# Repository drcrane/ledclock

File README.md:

LEDCLOCK
========

This repository contains the source files for my seven segment LED
Clock which I made in 2017 for my nephew.

The Clock is powered by an MSP430G2553 and a 32.768 kHz watch
crystal. The clock queried time over the serial port which should
be connected to an ESP8266 (ESP-01) running a modified terminal
programme that supports querying internet time servers.

Running ntpd on Alpine Linux
----------------------------

Turn on a time server in Alpine Linux / busybox (if compiled in)

    busybox ntpd -l -d -d -d -n

This is good for testing as you can see each request for the time.

ESP8266\_RTOS\_SDK
------------------

`esp8266terminal2` uses the espressif SDK, please see readme file
in `esp8266terminal2`.

 - Benjamin Green 2021-12-31

Open-RTOS-SDK
-------------

`esp8266terminal` is no longer used for this project and will be
removed soon. Please use `esp8266terminal2`.

The terminal application was modified (not very well) to support
this application. The REPOs:

repo:   https://github.com/SuperHouse/esp-open-rtos
commit: 46499c0f26c490f5a539f82eb950fa7879f65dc7

repo:   https://github.com/pfalcon/esp-open-sdk
commit: 5518fb6116c35a02ccb9a87260bb194a57cb429e

The build scripts and programmer are required from the above
repos.

The modified terminal application is available in:
`esp8266terminal` I recommend that you copy this into the
`esp-open-rtos/examples` directory to compile and deploy to
an ESP8266.

 - Benjamin Green 2018-02-03

Web Interface Time Setting
--------------------------

To set the time for a clock that currently has an IP address of `192.168.0.128`

    curl -v -d time_to_set=23:50:00 http://192.168.0.128/wifi

A browser may also be used by accessing the page at: `http://192.168.0.128/wifi`.

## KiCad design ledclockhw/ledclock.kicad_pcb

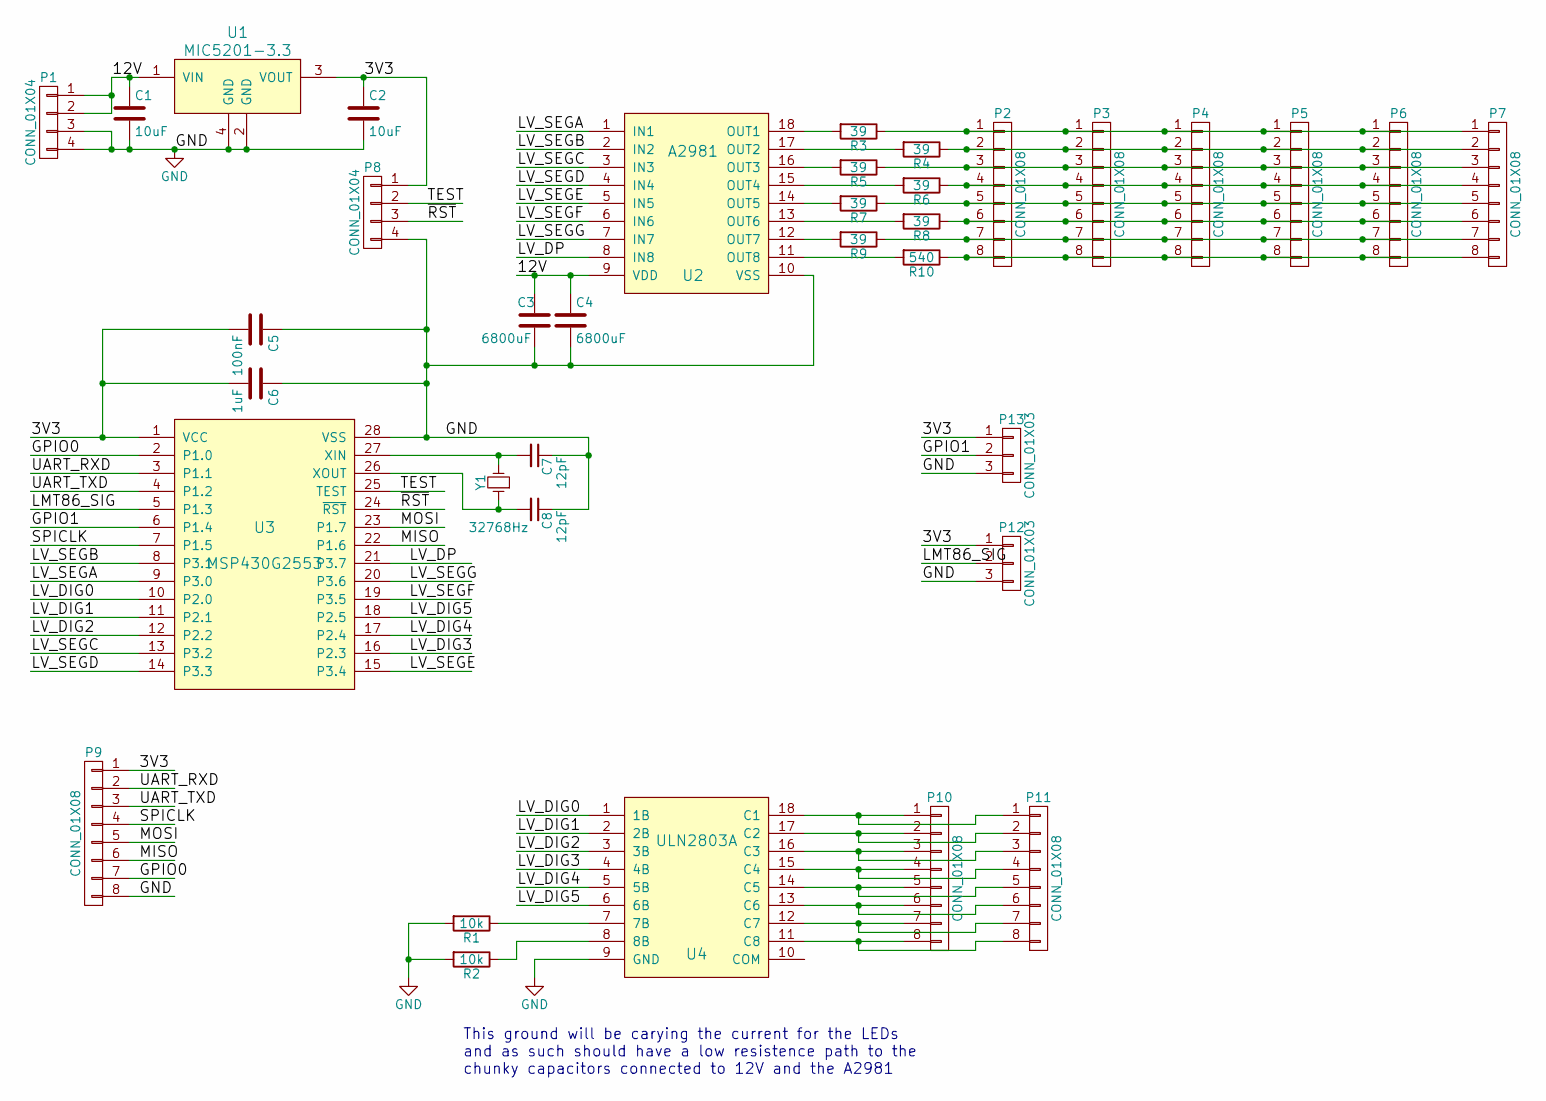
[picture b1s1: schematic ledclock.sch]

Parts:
C1, C2: 10uF; C_1210
C3, C4: 6800uF; CP_Radial_D18.0mm_P7.50mm
C5: 100nF; C_0603
C6: 1uF; C_0805
C7, C8: 12pF; C_0603
P1, P8: CONN_01X04; Molex_KK-6410-04_04x2.54mm_Straight
P2, P3, P4, P5, P6, P7, P9, P10, P11: CONN_01X08; Molex_KK-6410-08_08x2.54mm_Straight
P12, P13: CONN_01X03; Molex_KK-6410-03_03x2.54mm_Straight
R1, R2: 10k; R_0603
R3, R4, R5, R6, R7, R8, R9: 39; R_1206
R10: 540; R_1206
U1: MIC5201-3.3; SOT-223
U2: A2981; DIP-18_W7.62mm
U3: MSP430G2553; TSSOP-28_4.4x9.7mm_Pitch0.65mm
U4: ULN2803A; DIP-18_W7.62mm
Y1: 32768Hz; Crystal_C38-LF_d3.0mm_l8.0mm_Horizontal

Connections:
/3V3: C2.1, C5.2, C6.2, P8.1, P9.1, P12.1, P13.1, U1.3 (VOUT), U3.1 (VCC)
/12V: C1.1, C3.1, C4.1, P1.1, P1.2, U1.1 (VIN), U2.9 (VDD)
/GPIO0: P9.7, U3.2 (P1.0)
/GPIO1: P13.2, U3.6 (P1.4)
/LMT86_SIG: P12.2, U3.5 (P1.3)
/LV_DIG0: U3.10 (P2.0), U4.1 (1B)
/LV_DIG1: U3.11 (P2.1), U4.2 (2B)
/LV_DIG2: U3.12 (P2.2), U4.3 (3B)
/LV_DIG3: U3.16 (P2.3), U4.4 (4B)
/LV_DIG4: U3.17 (P2.4), U4.5 (5B)
/LV_DIG5: U3.18 (P2.5), U4.6 (6B)
/LV_DP: U2.8 (IN8), U3.21 (P3.7)
/LV_SEGA: U2.1 (IN1), U3.9 (P3.0)
/LV_SEGB: U2.2 (IN2), U3.8 (P3.1)
/LV_SEGC: U2.3 (IN3), U3.13 (P3.2)
/LV_SEGD: U2.4 (IN4), U3.14 (P3.3)
/LV_SEGE: U2.5 (IN5), U3.15 (P3.4)
/LV_SEGF: U2.6 (IN6), U3.19 (P3.5)
/LV_SEGG: U2.7 (IN7), U3.20 (P3.6)
/MISO: P9.6, U3.22 (P1.6)
/MOSI: P9.5, U3.23 (P1.7)
/SPICLK: P9.4, U3.7 (P1.5)
/TEST: P8.2, U3.25 (TEST)
/UART_RXD: P9.2, U3.3 (P1.1)
/UART_TXD: P9.3, U3.4 (P1.2)
/~RST: P8.3, U3.24 (~RST)
GND: C1.2, C2.2, C3.2, C4.2, C5.1, C6.1, C7.1, C8.1, P1.3, P1.4, P8.4, P9.8, P12.3, P13.3, R1.2, R2.2, U1.2 (GND), U1.4 (GND), U2.10 (VSS), U3.28 (VSS), U4.9 (GND)
unnamed: C7.2, U3.27 (XIN), Y1.2
unnamed: C8.2, U3.26 (XOUT), Y1.1
unnamed: P2.1, P3.1, P4.1, P5.1, P6.1, P7.1, R3.1
unnamed: P2.2, P3.2, P4.2, P5.2, P6.2, P7.2, R4.1
unnamed: P2.3, P3.3, P4.3, P5.3, P6.3, P7.3, R5.1
unnamed: P2.4, P3.4, P4.4, P5.4, P6.4, P7.4, R6.1
unnamed: P2.5, P3.5, P4.5, P5.5, P6.5, P7.5, R7.1
unnamed: P2.6, P3.6, P4.6, P5.6, P6.6, P7.6, R8.1
unnamed: P2.7, P3.7, P4.7, P5.7, P6.7, P7.7, R9.1
unnamed: P2.8, P3.8, P4.8, P5.8, P6.8, P7.8, R10.1
unnamed: P10.1, P11.1, U4.18 (C1)
unnamed: P10.2, P11.2, U4.17 (C2)
unnamed: P10.3, P11.3, U4.16 (C3)
unnamed: P10.4, P11.4, U4.15 (C4)
unnamed: P10.5, P11.5, U4.14 (C5)
unnamed: P10.6, P11.6, U4.13 (C6)
unnamed: P10.7, P11.7, U4.12 (C7)
unnamed: P10.8, P11.8, U4.11 (C8)
unnamed: R1.1, U4.7 (7B)
unnamed: R2.1, U4.8 (8B)
unnamed: R3.2, U2.18 (OUT1)
unnamed: R4.2, U2.17 (OUT2)
unnamed: R5.2, U2.16 (OUT3)
unnamed: R6.2, U2.15 (OUT4)
unnamed: R7.2, U2.14 (OUT5)
unnamed: R8.2, U2.13 (OUT6)
unnamed: R9.2, U2.12 (OUT7)
unnamed: R10.2, U2.11 (OUT8)

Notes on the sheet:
This ground will be carying the current for the LEDs and as such should have a low resistence path to the chunky capacitors connected to 12V and the A2981

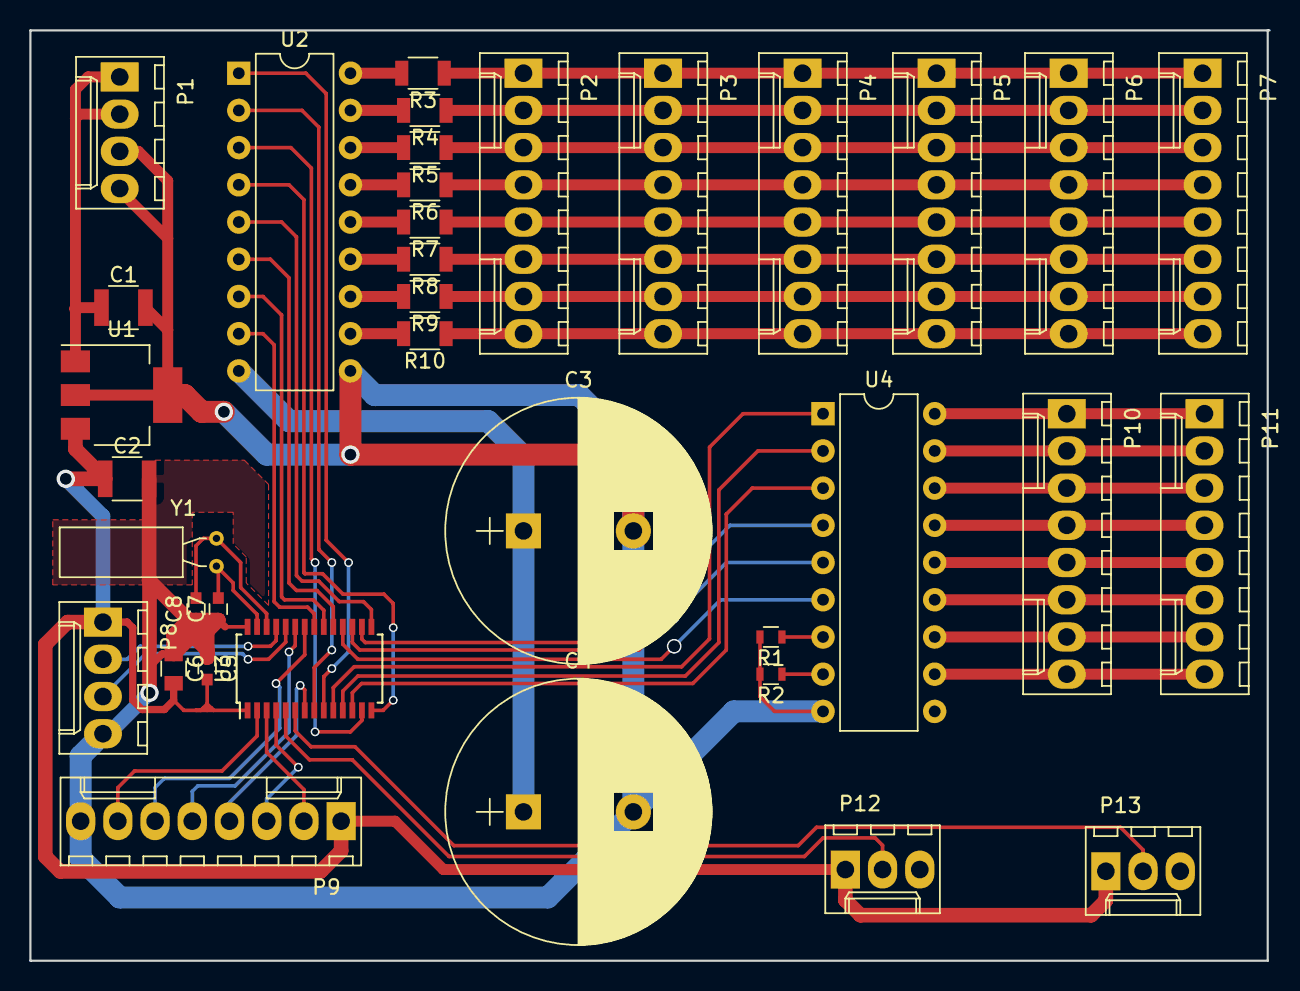
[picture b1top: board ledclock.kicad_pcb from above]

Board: 2 copper layers, 84.6 x 63.5 mm, 36 parts (0 on the bottom side), 55 nets.

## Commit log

2018-09-15 Setting Time via Serial Port
2018-09-16 Created some simple routines to determine correct time for DST
2018-09-16 Communication with ESP8266
2019-01-01 How to start busybox ntpd
2019-01-01 Cleanup and Simulator
    Added Simulator which will pretend to be the ESP8266
    listening for the MSP430 time requests.
2019-01-04 Drain the buffer of lines before calling select again
2019-01-05 Added ESP8266 Terminal
2019-05-11 Timezone logic was incorrect
2021-12-29 testing for argparser
2021-12-29 better handling of multiple spaces
2021-12-31 Migration to ESP8266_RTOS_SDK
2021-12-31 TCP Server WIP
2022-01-01 netconn style kind-of working
2022-01-01 simple non-blocking server example
2023-11-07 Code to make /wifi work to follow
2025-10-26 Begin dual AP/STA implementation
